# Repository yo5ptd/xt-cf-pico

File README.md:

# xt-cf-pico   
8-bit ISA interface for Compact Flash cards with a single PLD  

## Introduction

XT-CF-Pico is a remake of Sergey Kiselev  [xt-cf-lite-v4]  efectively reverting glue logic IC back to PLD but still using through hole components. This card allows connecting a Compact Flash (CF) card to computers with ISA bus and using it as a mass storage device. The card also supports BIOS extension ROM, but if you have it e.g. in a network adapter already, it's safe to leave it out.

* 16 KiB EEPROM (28128) with either 8 or 16k images, no flash ROM.
* no jumpers, everything you configure in the PLD (GAL20V8, still available on Aliexpress, used in projects like C64 PLA20V8)

This is my first ISA board and first PLD design, it was easy to debug by just rewriting the GAL and EPROM! My motivation was that there were too many components and a lot of unused pins on Sergey's design.

## Hardware Documentation
The idea was to use a minimum amount of components that were available late '80s, keeping Sergey's concept of having them all through hole (except of course the CF adapter). Result was one GAL IC and one EPROM.

Download latest bios from https://www.xtideuniversalbios.org/binaries/ (I used IDE_ATL.BIN) and configure primary IDE (with xtidecfg.com) for XT CF BIU 8 (I used addr 0x300).
[XTCFG](images/biu.jpg) 

### Schematic and PCB Layout

[Schematic](KiCad/XT-CF-Pico-Schematic.pdf)

[PCB Layout](KiCad/XT-CF-Pico-Board.pdf)

[Assembled](images/assembled.jpg)

### Bill of Materials

Component Type | Reference | Description                             | Quantity | Possible Sources and Notes
-------------- | --------- | --------------------------------------- | -------- | --------------------------
PCB            |           | XT-CF-Pico 	                           | 1        | jlpcb
Capacitor      | C1        | 0.1 uF ceramic, 5.0 mm lead spacing     | 1        | 
Capacitor      | C2 	     | 10 uF electrolytic, 6.3 mm lead spacing | 1        | 
LED            | D1        | 5 m (T-1) LED indicator                 | 1        | You can use 2 pin jumper holder for external led
Connector      | P1        | Compact Flash Card connector            | 1        | 101D-TAAA-R01 from ATTEND  (this was the cheapest now, footprint was updated)
Resistor       | R1        | 470 Ohm, 1/4 W                          | 1        | Mouser 291-470-RC
Resistor       | R3        | 1 kOhm, 1/4 W                           | 1        | Mouser 291-1K-RC
Resistor       | R4        | 5.6 kOhm, 1/4 W                         | 1        | Mouser 291-5.6K-RC
Resistor       | R2        | 10 kOhm, 1/4 W                          | 0        | Note: Do not install, kept for historic reasons only (card present detection?)
IC             | U1        | 27128 EEPROM                            | 1        | mbm27128
IC Socket      | U1        | 28 pin 600 mil (wide) DIP socket        | 1        | optional
IC Socket      | U2        | 24 pin 300 mil (narrow) DIP socket      | 1        | optional

### Cost estimate for 5 boards

* PCB - 4.17 USD including shipping jlpcb
* GAL20V8 - 3.47 USD including shipping aliexpress
* 28C128 - 5.49 USD including shipping aliexpress
* 101D-TAAA-R01 attend - 10.4 including shipping from tme
* passives - 1USD or less (you can order them from tme to save on shipping)

Results a cost of around 5 USD per board (not including labor to assemble and program)

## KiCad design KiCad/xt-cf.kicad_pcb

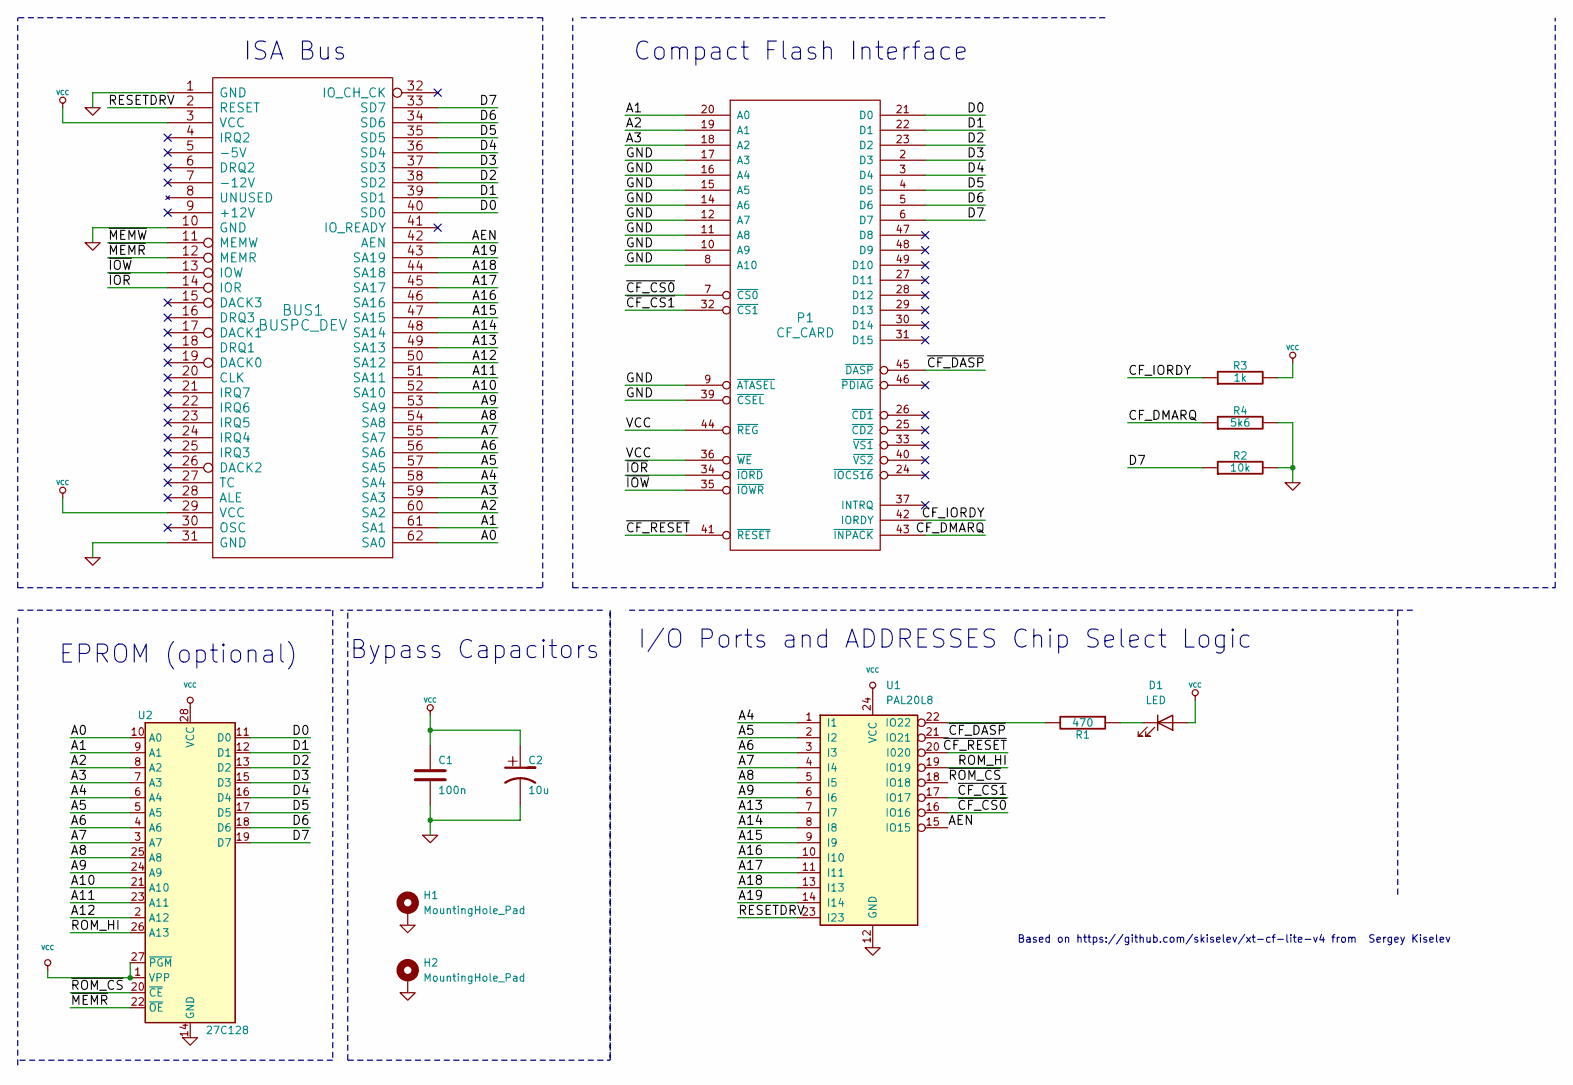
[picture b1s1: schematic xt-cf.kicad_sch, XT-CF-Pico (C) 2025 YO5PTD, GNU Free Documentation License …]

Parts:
BUS1: BUSPC_DEV; Conn_Bus_ISA8
C1: 100n; C_Disc_D5.0mm_W2.5mm_P5.00mm
C2: 10u; CP_Radial_D6.3mm_P2.50mm
D1: LED; LED_D5.0mm
H1, H2: MountingHole_Pad; MountingHole_3.2mm_M3_ISO7380_Pad
P1: CF_CARD; CF_N7E50-Q516XX-40
R1: 470; R_Axial_DIN0309_L9.0mm_D3.2mm_P15.24mm_Horizontal
R2: 10k; R_Axial_DIN0309_L9.0mm_D3.2mm_P15.24mm_Horizontal
R3: 1k; R_Axial_DIN0309_L9.0mm_D3.2mm_P15.24mm_Horizontal
R4: 5k6; R_Axial_DIN0309_L9.0mm_D3.2mm_P15.24mm_Horizontal
U1: PAL20L8; CERDIP-24_W7.62mm_SideBrazed_LongPads_Socket
U2: 27C128; DIP-28_W15.24mm_Socket_LongPads

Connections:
/A0: BUS1.62 (SA0), U2.10 (A0)
/A1: BUS1.61 (SA1), P1.20 (A0), U2.9 (A1)
/A2: BUS1.60 (SA2), P1.19 (A1), U2.8 (A2)
/A3: BUS1.59 (SA3), P1.18 (A2), U2.7 (A3)
/A4: BUS1.58 (SA4), U1.1 (I1), U2.6 (A4)
/A5: BUS1.57 (SA5), U1.2 (I2), U2.5 (A5)
/A6: BUS1.56 (SA6), U1.3 (I3), U2.4 (A6)
/A7: BUS1.55 (SA7), U1.4 (I4), U2.3 (A7)
/A8: BUS1.54 (SA8), U1.5 (I5), U2.25 (A8)
/A9: BUS1.53 (SA9), U1.6 (I6), U2.24 (A9)
/A10: BUS1.52 (SA10), U2.21 (A10)
/A11: BUS1.51 (SA11), U2.23 (A11)
/A12: BUS1.50 (SA12), U2.2 (A12)
/A13: BUS1.49 (SA13), U1.7 (I7)
/A14: BUS1.48 (SA14), U1.8 (I8)
/A15: BUS1.47 (SA15), U1.9 (I9)
/A16: BUS1.46 (SA16), U1.10 (I10)
/A17: BUS1.45 (SA17), U1.11 (I11)
/A18: BUS1.44 (SA18), U1.13 (I13)
/A19: BUS1.43 (SA19), U1.14 (I14)
/AEN: BUS1.42 (AEN), U1.15 (IO15)
/CF_DMARQ: P1.43 (~INPACK), R4.1
/CF_IORDY: P1.42 (IORDY), R3.1
/D0: BUS1.40 (SD0), P1.21 (D0), U2.11 (D0)
/D1: BUS1.39 (SD1), P1.22 (D1), U2.12 (D1)
/D2: BUS1.38 (SD2), P1.23 (D2), U2.13 (D2)
/D3: BUS1.37 (SD3), P1.2 (D3), U2.15 (D3)
/D4: BUS1.36 (SD4), P1.3 (D4), U2.16 (D4)
/D5: BUS1.35 (SD5), P1.4 (D5), U2.17 (D5)
/D6: BUS1.34 (SD6), P1.5 (D6), U2.18 (D6)
/D7: BUS1.33 (SD7), P1.6 (D7), R2.1, U2.19 (D7)
/RESETDRV: BUS1.2 (RESET), U1.23 (I23)
/ROM_HI: U1.19 (IO19), U2.26 (A13)
/~CF_CS0: P1.7 (~CS0), U1.16 (IO16)
/~CF_CS1: P1.32 (~CS1), U1.17 (IO17)
/~CF_DASP: P1.45 (~DASP), U1.21 (IO21)
/~CF_RESET: P1.41 (~RESET), U1.20 (I020)
/~IOR: BUS1.14 (IOR), P1.34 (~IORD)
/~IOW: BUS1.13 (IOW), P1.35 (~IOWR)
/~MEMR: BUS1.12 (MEMR), U2.22 (~OE)
/~MEMW: BUS1.11 (MEMW)
/~ROM_CS: U1.18 (IO18), U2.20 (~CE)
GND: BUS1.1 (GND), BUS1.10 (GND), BUS1.31 (GND), C1.2, C2.2, H1.1, H2.1, P1.1 (GND), P1.8 (A10), P1.9 (~ATASEL), P1.10 (A9), P1.11 (A8), P1.12 (A7), P1.14 (A6), P1.15 (A5), P1.16 (A4), P1.17 (A3), P1.39 (~CSEL), P1.50 (GND), R2.2, R4.2, U1.12 (GND), U2.14 (GND)
unnamed: D1.1 (K), R1.1
unnamed: R1.2, U1.22 (IO22)
VCC: BUS1.3 (VCC), BUS1.29 (VCC), C1.1, C2.1, D1.2 (A), P1.13 (VCC), P1.36 (~WE), P1.38 (VCC), P1.44 (~REG), R3.2, U1.24 (VCC), U2.1 (VPP), U2.27 (~PGM), U2.28 (VCC)

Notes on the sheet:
ISA Bus
Bypass Capacitors
Based on https://github.com/skiselev/xt-cf-lite-v4 from Sergey Kiselev
I/O Ports and ADDRESSES Chip Select Logic
EPROM (optional)
Compact Flash Interface

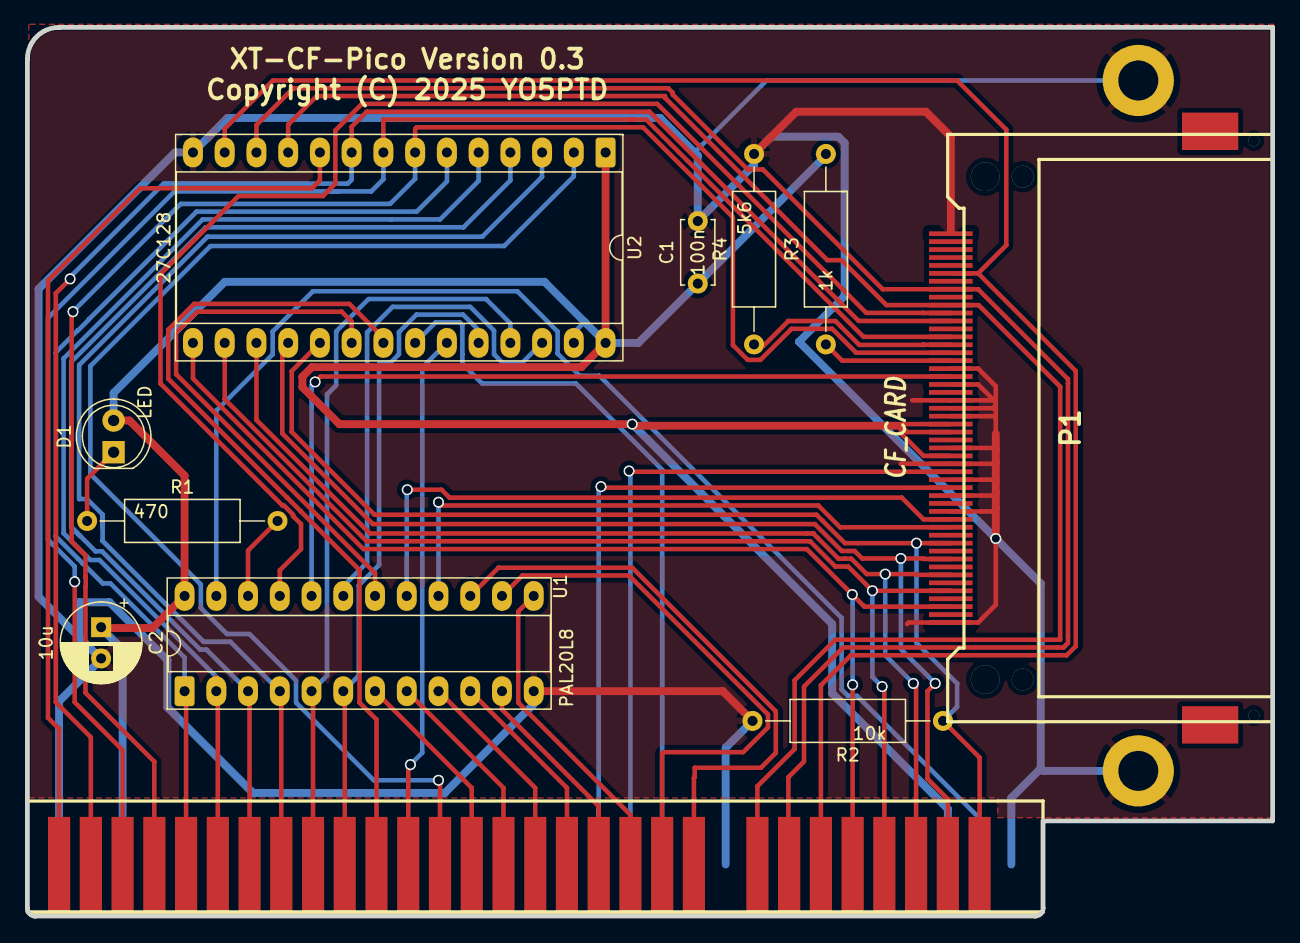
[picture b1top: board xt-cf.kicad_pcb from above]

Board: 2 copper layers, 99.7 x 71.1 mm, 13 parts (0 on the bottom side), 45 nets.

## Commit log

2025-03-25 Added PLD file
2025-03-27 Some touchups, gerbers that were sent to JLPCB ver 0.2
2025-04-07 Corrected inverted address pins in PLD, some readme
2025-04-08 Major fixes to PLD
2025-04-08 fixes
2025-04-08 Added 3d printed bracket
2025-04-10 Final, tested version
    CF Card detected
2025-05-08 Fix for PLD A4 - read reliability issues

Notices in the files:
KiCad/xt-cf.kicad_pcb:
Copyright (C) 2025 YO5PTD
KiCad/xt-cf.kicad_sch:
XT-CF-Pico (C) 2025 YO5PTD, GNU Free Documentation License (GFDL)
